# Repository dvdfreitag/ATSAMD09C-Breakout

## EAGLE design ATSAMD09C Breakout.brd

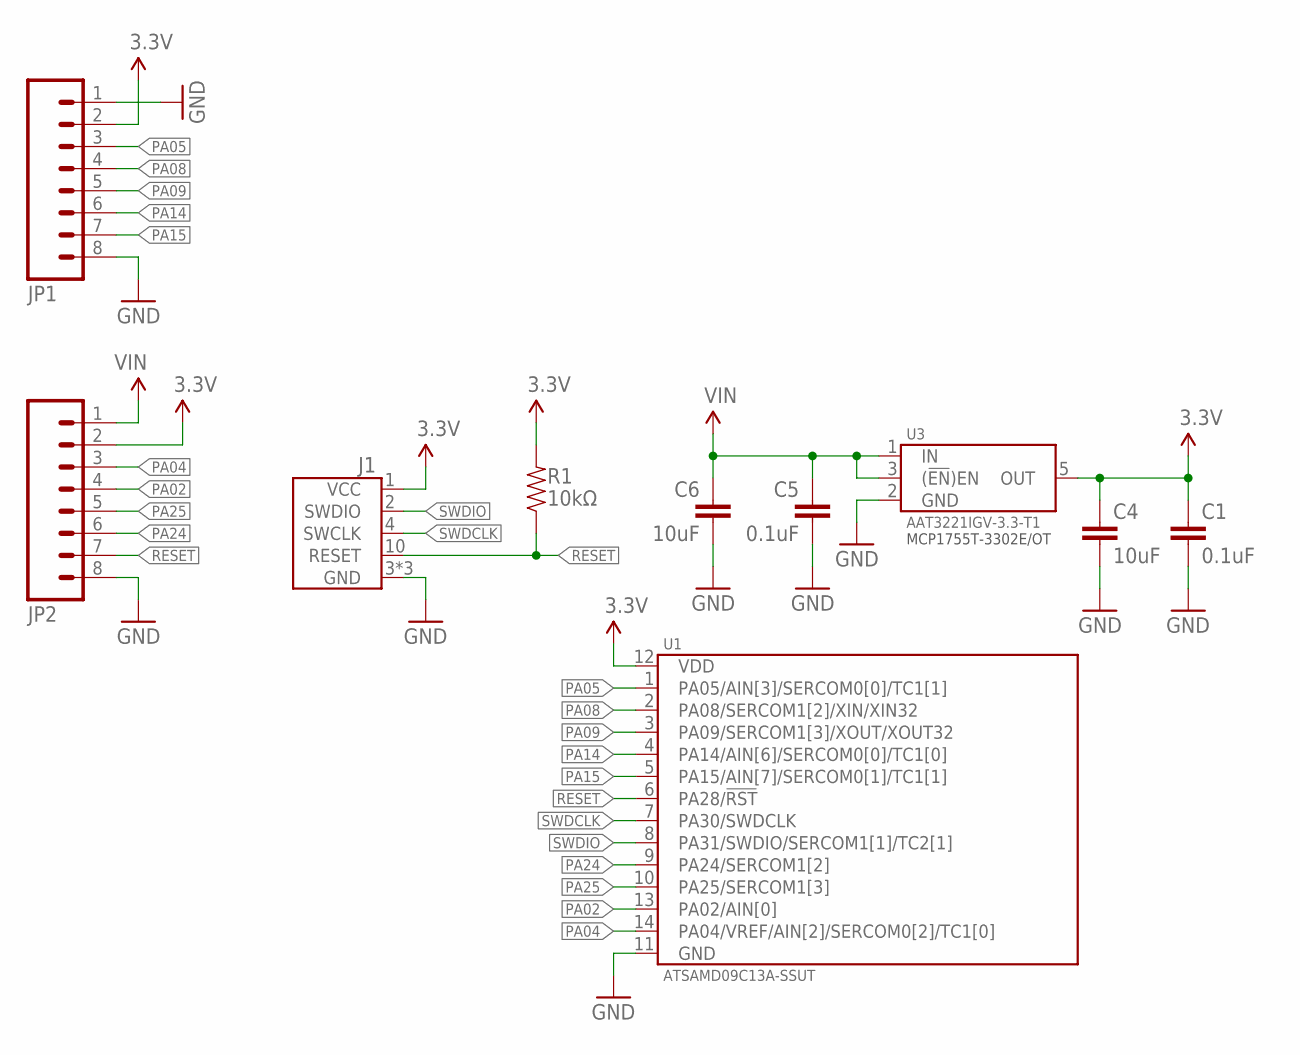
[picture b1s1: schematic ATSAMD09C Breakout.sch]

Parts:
C1, C5: 0.1uF; 0805-CAP
C4, C6: 10uF; 0805-CAP
J1: SWD-50MIL-SHROUDED; M05X2_50MIL_SHROUDED
JP1, JP2: M08NO_SILK; 1X08_NO_SILK
R1: 10kΩ; 0805-RES
U1: ATSAMD09C13A-SSUT; SOIC-14
U3: AAT3221IGV-3.3-T1; SOT23-5

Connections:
3.3V: C1.1, C4.1, J1.1 (VCC), JP1.2, JP2.2, R1.2, U1.12 (VDD), U3.5 (OUT)
GND: C1.2, C4.2, C5.2, C6.2, J1.3 (GND), J1.5 (GND), J1.9 (GND), JP1.1, JP1.8, JP2.8, U1.11 (GND), U3.2 (GND)
PA02: JP2.4, U1.13 (PA02/AIN[0])
PA04: JP2.3, U1.14 (PA04/VREF/AIN[2]/SERCOM0[2]/TC1[0])
PA05: JP1.3, U1.1 (PA05/AIN[3]/SERCOM0[0]/TC1[1])
PA08: JP1.4, U1.2 (PA08/SERCOM1[2]/XIN/XIN32)
PA09: JP1.5, U1.3 (PA09/SERCOM1[3]/XOUT/XOUT32)
PA14: JP1.6, U1.4 (PA14/AIN[6]/SERCOM0[0]/TC1[0])
PA15: JP1.7, U1.5 (PA15/AIN[7]/SERCOM0[1]/TC1[1])
PA24: JP2.6, U1.9 (PA24/SERCOM1[2])
PA25: JP2.5, U1.10 (PA25/SERCOM1[3])
RESET: J1.10 (RESET), JP2.7, R1.1, U1.6 (PA28/!RST)
SWDCLK: J1.4 (SWCLK), U1.7 (PA30/SWDCLK)
SWDIO: J1.2 (SWDIO), U1.8 (PA31/SWDIO/SERCOM1[1]/TC2[1])
VIN: C5.1, C6.1, JP2.1, U3.1 (IN), U3.3 ((!EN!)EN)

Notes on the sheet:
MCP1755T-3302E/OT

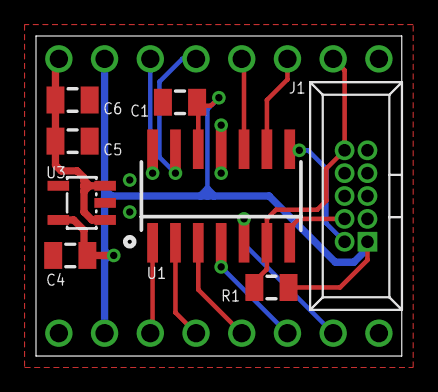
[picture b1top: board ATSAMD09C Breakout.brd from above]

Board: 2 copper layers, 20.3 x 17.8 mm, 10 parts (0 on the bottom side), 15 nets.

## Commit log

2016-08-11 Create LICENSE

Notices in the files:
parts and their libraries:
SparkFun-Connectors: Licensing: Creative Commons ShareAlike 4.0 International - https://creativecommons.org/licenses/by-sa/4.0
